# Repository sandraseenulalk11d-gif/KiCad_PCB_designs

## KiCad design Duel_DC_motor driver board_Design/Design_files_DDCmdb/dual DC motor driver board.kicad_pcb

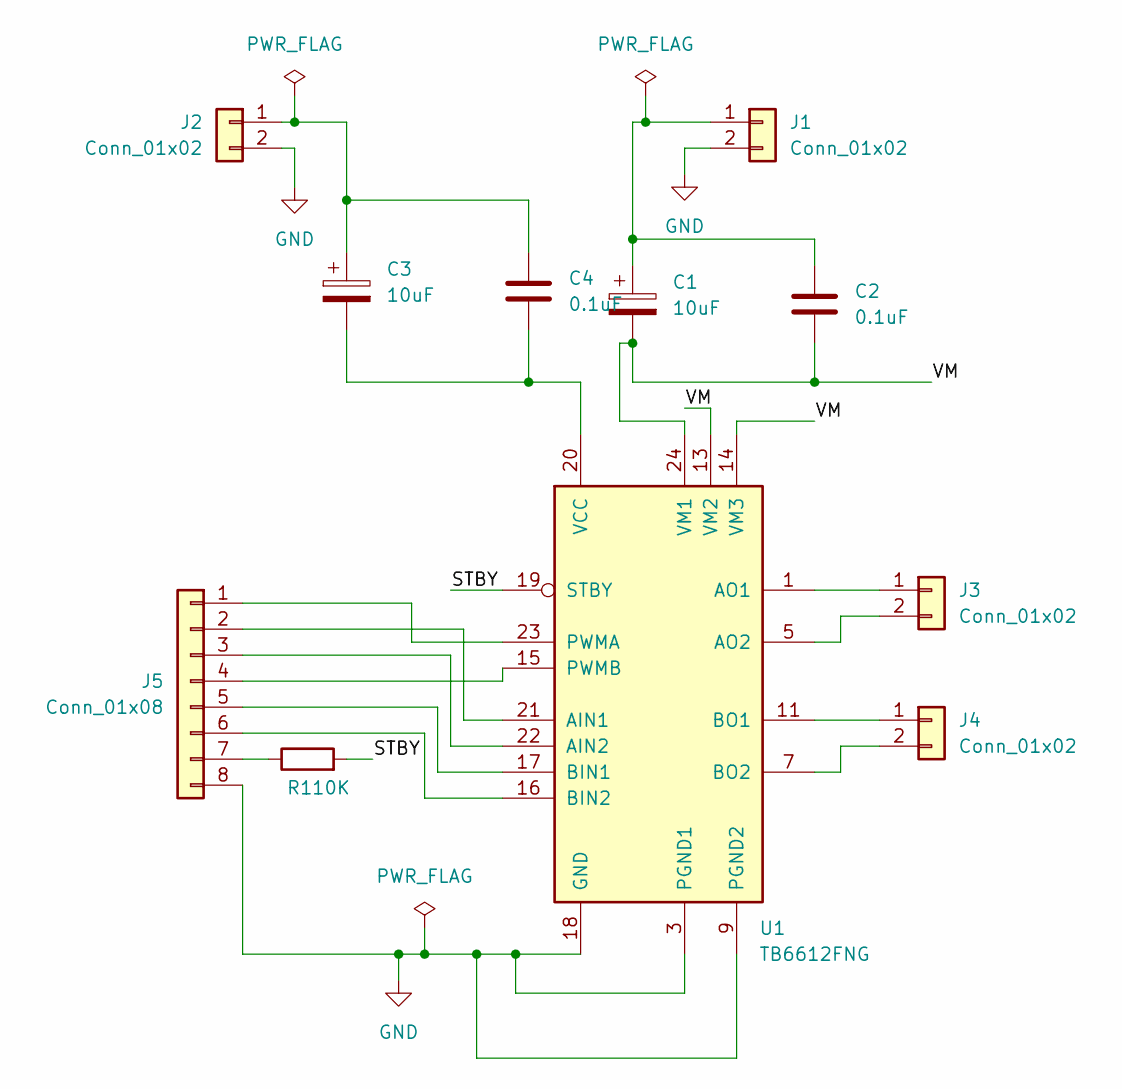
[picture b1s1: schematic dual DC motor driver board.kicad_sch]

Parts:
C1, C3: 10uF; CP_Radial_D5.0mm_P2.00mm
C2, C4: 0.1uF; C_0805_2012Metric
J1, J2, J3, J4: Conn_01x02; JST_XH_B2B-XH-A_1x02_P2.50mm_Vertical
J5: Conn_01x08; PinHeader_1x08_P2.54mm_Vertical
R1: 10K; R_0805_2012Metric
U1: TB6612FNG; SSOP-24_5.3x8.2mm_P0.65mm

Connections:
/STBY: R1.2, U1.19 (STBY)
/VM: C1.2, C2.2, U1.13 (VM2), U1.14 (VM3), U1.24 (VM1)
GND: J1.2, J2.2, J5.8, U1.3 (PGND1), U1.4 (PGND1), U1.9 (PGND2), U1.10 (PGND2), U1.18 (GND)
unnamed: C1.1, C2.1, J1.1
unnamed: C3.1, C4.1, J2.1
unnamed: J3.1, U1.1 (AO1), U1.2 (AO1)
unnamed: J3.2, U1.5 (AO2), U1.6 (AO2)
unnamed: J4.1, U1.11 (BO1), U1.12 (BO1)
unnamed: J4.2, U1.7 (BO2), U1.8 (BO2)
unnamed: J5.1, U1.23 (PWMA)
unnamed: J5.2, U1.21 (AIN1)
unnamed: J5.3, U1.22 (AIN2)
unnamed: J5.4, U1.15 (PWMB)
unnamed: J5.5, U1.17 (BIN1)
unnamed: J5.6, U1.16 (BIN2)
unnamed: J5.7, R1.1
unnamed: C3.2, C4.2, U1.20 (VCC)

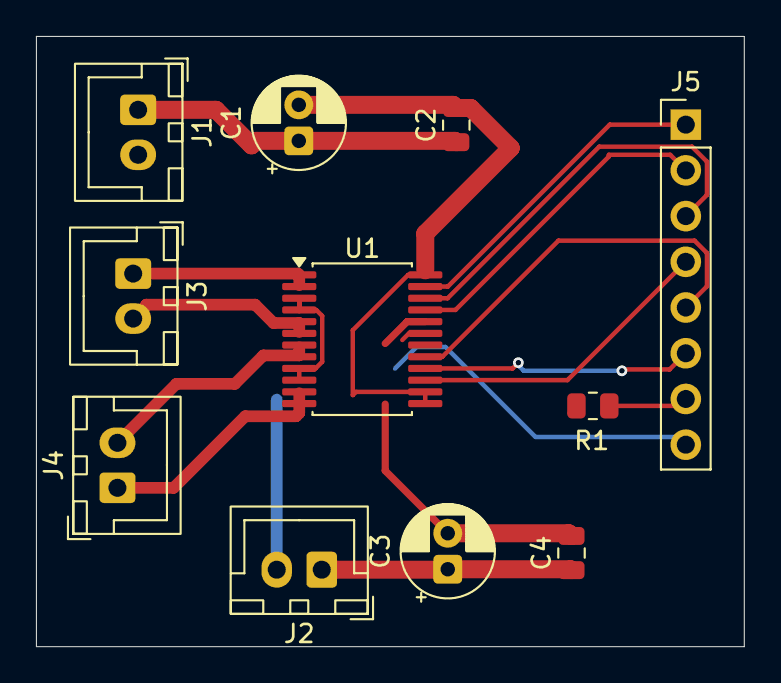
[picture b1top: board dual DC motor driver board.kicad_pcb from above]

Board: 2 copper layers, 39.3 x 33.9 mm, 11 parts (0 on the bottom side), 17 nets.

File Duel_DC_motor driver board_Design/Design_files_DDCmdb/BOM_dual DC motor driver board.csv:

"Reference","Qty","Value","DNP","Exclude from BOM","Exclude from Board","Footprint","Datasheet"
"C1,C3","2","10uF","","","","Capacitor_THT:CP_Radial_D5.0mm_P2.00mm",""
"C2,C4","2","0.1uF","","","","Capacitor_SMD:C_0805_2012Metric",""
"J1,J2,J3,J4","4","Conn_01x02","","","","Connector_JST:JST_XH_B2B-XH-A_1x02_P2.50mm_Vertical",""
"J5","1","Conn_01x08","","","","Connector_PinHeader_2.54mm:PinHeader_1x08_P2.54mm_Vertical",""
"R1","1","10K","","","","Resistor_SMD:R_0805_2012Metric",""
"U1","1","TB6612FNG","","","","Package_SO:SSOP-24_5.3x8.2mm_P0.65mm","https://toshiba.semicon-storage.com/us/product/linear/motord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"

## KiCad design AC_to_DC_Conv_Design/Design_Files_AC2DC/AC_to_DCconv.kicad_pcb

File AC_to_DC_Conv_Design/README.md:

# 230V AC to 5V DC Transformerless Power Supply

A compact, non-isolated capacitive dropper AC-DC power supply designed to provide low-current DC rails for microcontrollers and embedded sensors directly from single-phase utility mains.

---

## Technical Specifications

| Parameter | Value |
| :--- | :--- |
| **Input Voltage** | 230V AC ±10%, 50 Hz |
| **Output Voltage** | 5V DC (clamped and filtered) |
| **Output Current** | 30 mA – 40 mA continuous |
| **Topology** | Series capacitive dropper with full-bridge rectification and Zener shunt regulator |
| **Cooling** | Passive convection |

---

## Circuit Working & Key Stages

* **Capacitive Dropping Stage:** Uses the AC reactance ($X_C = \frac{1}{2\pi f C}$) of a high-voltage film capacitor to drop the mains voltage without the resistive heat dissipation of standard dropper resistors.
* **Transient & Inrush Suppression:** A flameproof fusible wirewound resistor limits high inrush current spikes during mains switch-on, paired with a metal-oxide varistor (MOV) to clamp utility voltage transients.
* **Discharge Mechanism:** A high-value bleeder resistor connected across the AC dropper capacitor ensures rapid discharge of stored energy when disconnected from mains.
* **Rectification & Filtering:** A full-wave diode bridge converts AC to pulsating DC, followed by an electrolytic reservoir capacitor with low ESR to smooth voltage ripple.
* **Regulation:** A precision Zener diode clamps the output rail, maintaining stable DC regulation across changing load currents.

---

## High-Voltage Safety Guidelines

* **Galvanic Isolation Warning:** This design contains **no isolation transformer**. The output DC ground rail floats directly at AC mains line potential.
* **Operational Hazard:** Direct contact with any point on this board during operation poses a severe electric shock risk.
* **Testing Requirement:** Always use an **isolated AC source (isolation transformer)** and an insulated probe setup during bench debugging and oscilloscope measurements.
* **Enclosure:** This module must be housed in a non-conductive, sealed plastic enclosure (flame-retardant ABS or polycarbonate) with no exposed metal headers or test pins.

---

## Repository Contents

* `/Design_Files_AC2DC` — Complete KiCad schematic (`.kicad_sch`), PCB layout (`.kicad_pcb`), and project configuration.
* `/Gerbers_AC2DC` — Production-ready Gerber files (copper layers, solder mask, silkscreen, and drill files).

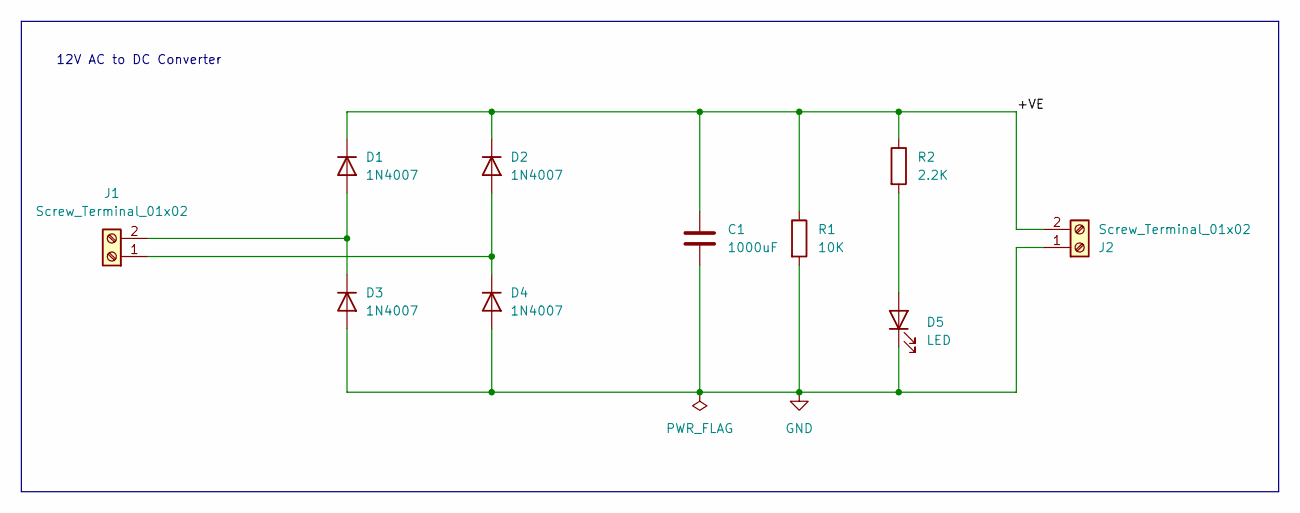
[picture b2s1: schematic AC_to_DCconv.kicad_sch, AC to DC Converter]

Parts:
C1: 1000uF; C_Radial_D8.0mm_H11.5mm_P3.50mm
D1, D2, D3, D4: 1N4007; D_DO-41_SOD81_P10.16mm_Horizontal
D5: LED; LED_D5.0mm
J1, J2: Screw_Terminal_01x02; TerminalBlock_Phoenix_MKDS-1,5-2-5.08_1x02_P5.08mm_Horizont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
R1: 10K; R_Axial_DIN0204_L3.6mm_D1.6mm_P7.62mm_Horizontal
R2: 2.2K; R_Axial_DIN0204_L3.6mm_D1.6mm_P7.62mm_Horizontal

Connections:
/+VE: C1.1, D1.1 (K), D2.1 (K), J2.2, R1.1, R2.1
GND: C1.2, D3.2 (A), D4.2 (A), D5.1 (K), J2.1, R1.2
unnamed: D1.2 (A), D3.1 (K), J1.2
unnamed: D2.2 (A), D4.1 (K), J1.1
unnamed: D5.2 (A), R2.2

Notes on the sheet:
12V AC to DC Converter

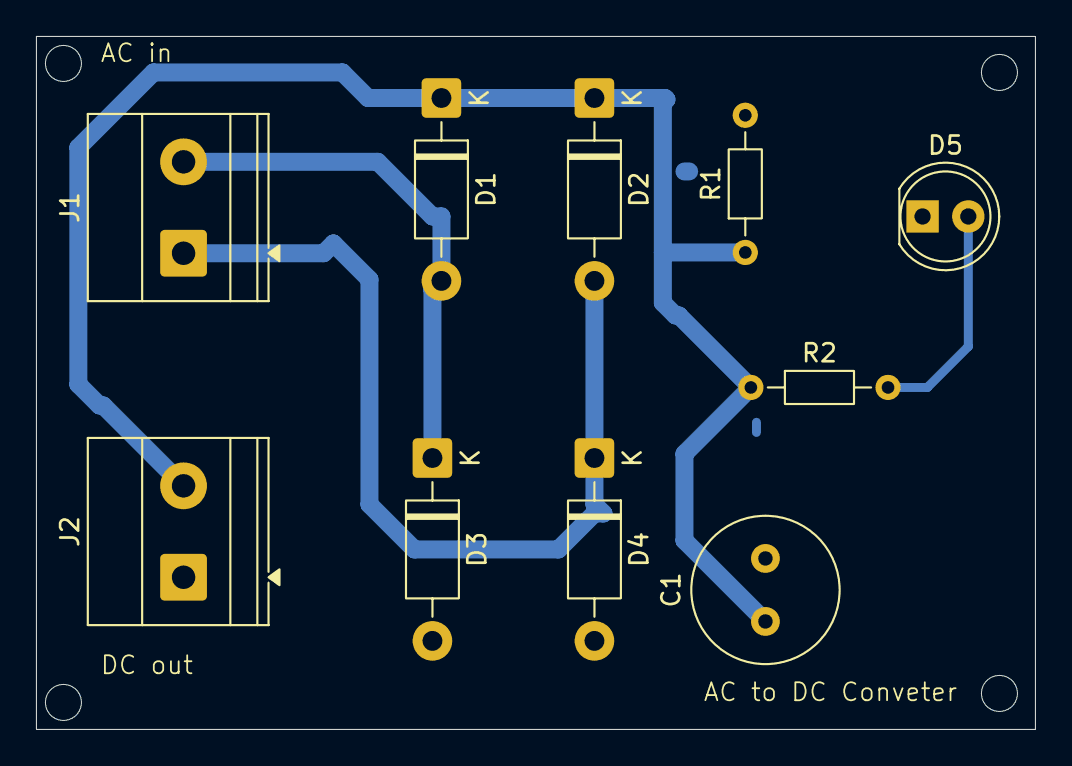
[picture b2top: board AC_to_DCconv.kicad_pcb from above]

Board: 2 copper layers, 55.5 x 38.5 mm, 10 parts (0 on the bottom side), 5 nets.

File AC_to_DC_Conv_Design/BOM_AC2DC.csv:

"Reference","Qty","Value","DNP","Exclude from BOM","Exclude from Board","Footprint","Datasheet"
"C1","1","1000uF","","","","Capacitor_THT:C_Radial_D8.0mm_H11.5mm_P3.50mm",""
"D1,D2,D3,D4","4","1N4007","","","","Diode_THT:D_DO-41_SOD81_P10.16mm_Horizontal","http://www.vishay.com/docs/88503/1n4001.pdf"
"D5","1","LED","","","","LED_THT:LED_D5.0mm",""
"J1,J2","2","Screw_Terminal_01x02","","","","TerminalBlock_Phoenix:TerminalBlock_Phoenix_MKDS-1,5-2-5.08_1x02_P5.08mm_Horizontal",""
"R1","1","10K","","","","Resistor_THT:R_Axial_DIN0204_L3.6mm_D1.6mm_P7.62mm_Horizontal",""
"R2","1","2.2K","","","","Resistor_THT:R_Axial_DIN0204_L3.6mm_D1.6mm_P7.62mm_Horizontal",""

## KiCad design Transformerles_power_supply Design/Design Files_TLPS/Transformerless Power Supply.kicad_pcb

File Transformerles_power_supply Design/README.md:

# Non-Isolated Capacitive Dropper Power Supply

A compact, transformerless AC-DC power supply designed to power low-current microcontroller and sensor circuits directly from 230V AC mains.

## Technical Specifications
- **Input Voltage:** 230V AC @ 50 Hz
- **Output:** 5V DC / ~30-50 mA
- **Topology:** Capacitive dropper with bridge rectification and Zener shunt regulation

## Safety & Component Implementation
- **Dropping Element:** Metallized polypropylene X2 safety capacitor
- **Shock Protection:** Bleeder resistor for passive capacitive discharge on disconnect
- **Transient & Surge Handling:** Inrush surge limiter resistor + MOV overvoltage clamp
- **Isolation Note:** Non-isolated topology; designed strictly for fully enclosed, touch-safe enclosures.

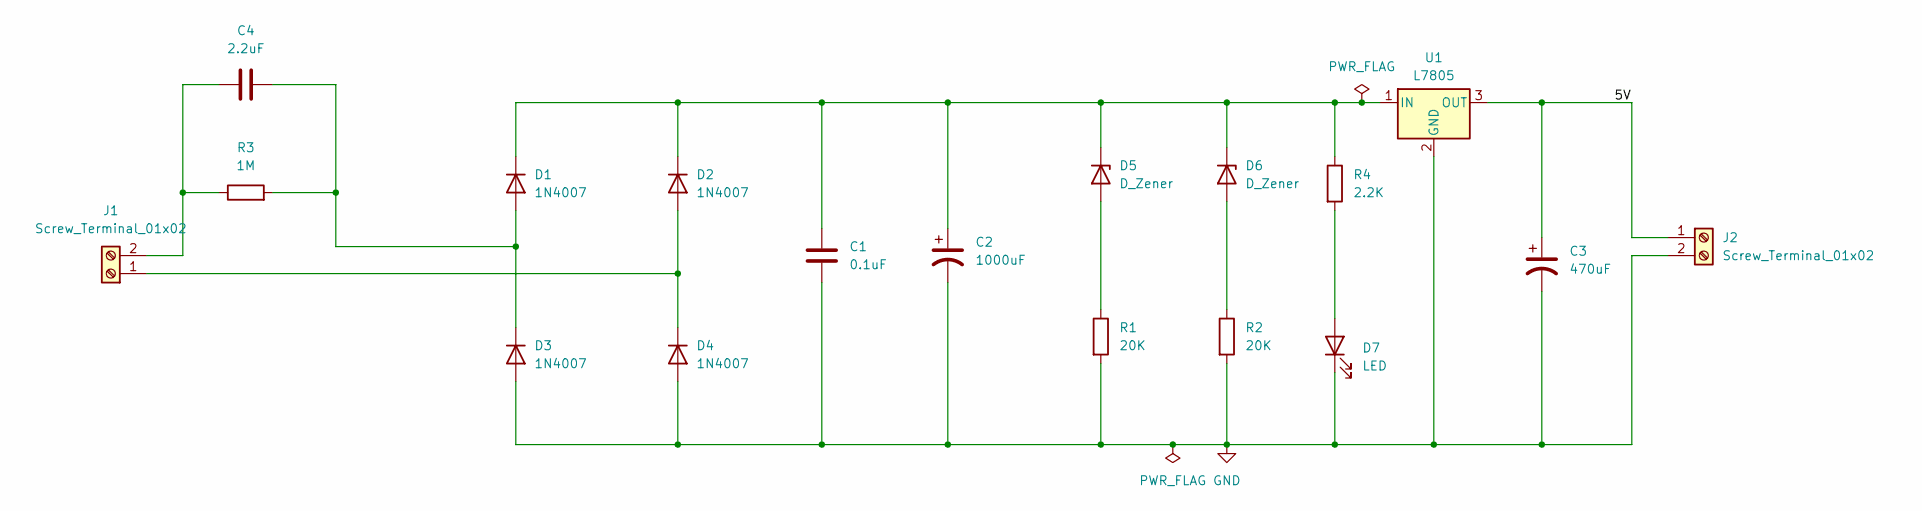
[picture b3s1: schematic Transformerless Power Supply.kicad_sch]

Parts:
C1: 0.1uF; C_Disc_D4.7mm_W2.5mm_P5.00mm
C2: 1000uF; CP_Radial_D10.0mm_P5.00mm
C3: 470uF; CP_Radial_D10.0mm_P3.80mm
C4: 2.2uF; C_Rect_L18.0mm_W6.0mm_P15.00mm_FKS3_FKP3
D1, D2, D3, D4: 1N4007; D_DO-41_SOD81_P10.16mm_Horizontal
D5, D6: D_Zener; D_A-405_P7.62mm_Horizontal
D7: LED; LED_D5.0mm
J1, J2: Screw_Terminal_01x02; TerminalBlock_Phoenix_MKDS-1,5-2-5.08_1x02_P5.08mm_Horizont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
R1, R2: 20K; R_Axial_DIN0207_L6.3mm_D2.5mm_P7.62mm_Horizontal
R3: 1M; R_Axial_DIN0207_L6.3mm_D2.5mm_P7.62mm_Horizontal
R4: 2.2K; R_Axial_DIN0207_L6.3mm_D2.5mm_P7.62mm_Horizontal
U1: L7805; TO-220-3_Vertical

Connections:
/5V: C3.1, J2.1, U1.3 (OUT)
GND: C1.2, C2.2, C3.2, D3.2 (A), D4.2 (A), D7.1 (K), J2.2, R1.2, R2.2, U1.2 (GND)
unnamed: C4.1, D1.2 (A), D3.1 (K), R3.2
unnamed: C1.1, C2.1, D1.1 (K), D2.1 (K), D5.1 (K), D6.1 (K), R4.1, U1.1 (IN)
unnamed: D2.2 (A), D4.1 (K), J1.1
unnamed: D5.2 (A), R1.1
unnamed: D6.2 (A), R2.1
unnamed: D7.2 (A), R4.2
unnamed: C4.2, J1.2, R3.1

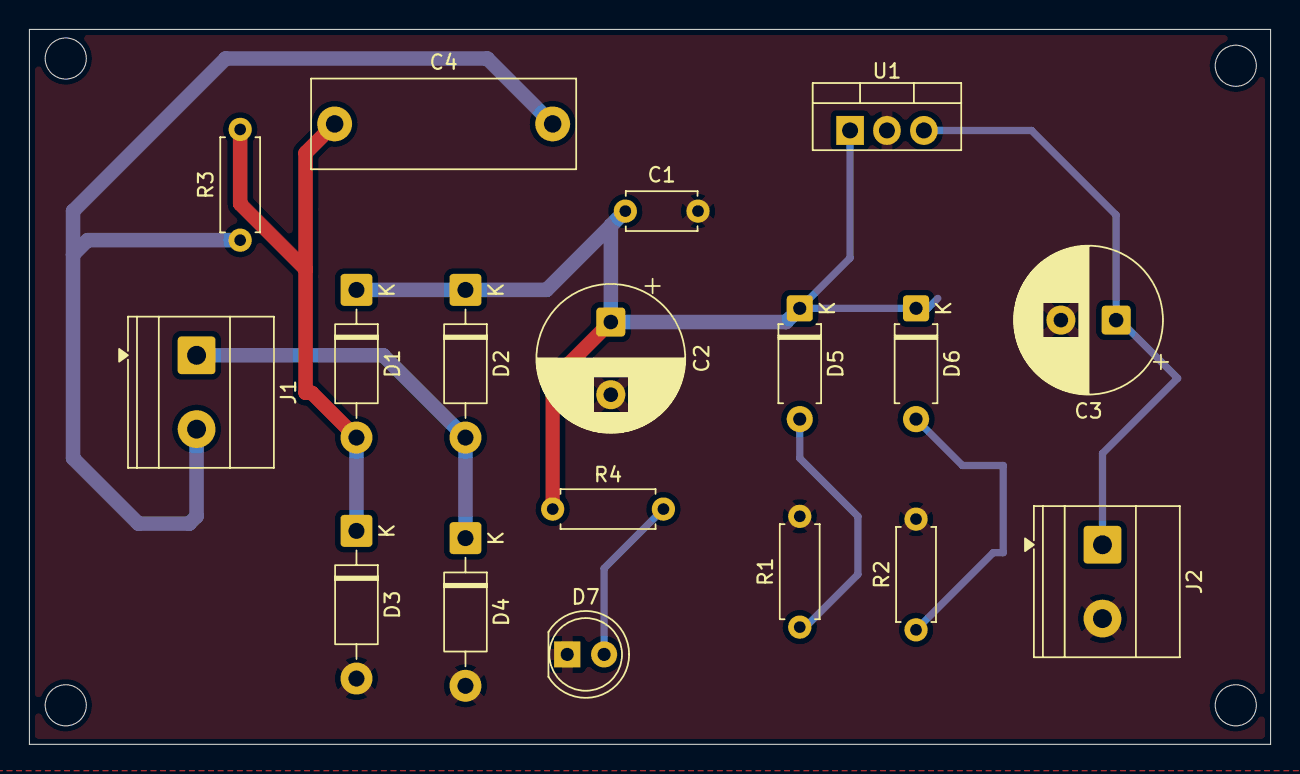
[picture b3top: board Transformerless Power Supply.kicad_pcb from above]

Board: 2 copper layers, 85.4 x 49.2 mm, 18 parts (0 on the bottom side), 9 nets.

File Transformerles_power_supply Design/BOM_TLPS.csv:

"Reference","Qty","Value","DNP","Exclude from BOM","Exclude from Board","Footprint","Datasheet"
"C1","1","0.1uF","","","","Capacitor_THT:C_Disc_D4.7mm_W2.5mm_P5.00mm",""
"C2","1","1000uF","","","","Capacitor_THT:CP_Radial_D10.0mm_P5.00mm",""
"C3","1","470uF","","","","Capacitor_THT:CP_Radial_D10.0mm_P3.80mm",""
"C4","1","2.2uF","","","","Capacitor_THT:C_Rect_L18.0mm_W6.0mm_P15.00mm_FKS3_FKP3",""
"D1,D2,D3,D4","4","1N4007","","","","Diode_THT:D_DO-41_SOD81_P10.16mm_Horizontal","http://www.vishay.com/docs/88503/1n4001.pdf"
"D5,D6","2","D_Zener","","","","Diode_THT:D_A-405_P7.62mm_Horizontal",""
"D7","1","LED","","","","LED_THT:LED_D5.0mm",""
"J1,J2","2","Screw_Terminal_01x02","","","","TerminalBlock_Phoenix:TerminalBlock_Phoenix_MKDS-1,5-2-5.08_1x02_P5.08mm_Horizontal",""
"R1,R2","2","20K","","","","Resistor_THT:R_Axial_DIN0207_L6.3mm_D2.5mm_P7.62mm_Horizontal",""
"R3","1","1M","","","","Resistor_THT:R_Axial_DIN0207_L6.3mm_D2.5mm_P7.62mm_Horizontal",""
"R4","1","2.2K","","","","Resistor_THT:R_Axial_DIN0207_L6.3mm_D2.5mm_P7.62mm_Horizontal",""
"U1","1","L7805","","","","Package_TO_SOT_THT:TO-220-3_Vertical","http://www.st.com/content/ccc/resource/technical/document/da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"

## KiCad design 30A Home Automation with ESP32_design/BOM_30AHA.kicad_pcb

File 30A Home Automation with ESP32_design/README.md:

# ESP32 30A Home Automation Controller

A custom industrial-grade controller board featuring ESP32 control, optoisolated relay driving, and GSM connectivity.

## Specifications & Features
- **Microcontroller:** ESP32-WROOM-32 (Wi-Fi / BLE)
- **Power Switching:** 30A high-power relays with PC817 optocoupler isolation
- **Cellular Connectivity:** SIM800 / Mini-SIM socket integration
- **Protection:** Flyback diodes, TVS diode arrays on I/O, and creepage isolation slots

## Repository Contents
- `/Design_files_30AHA`: KiCad schematic (`.kicad_sch`) and layout (`.kicad_pcb`)
- `/Gerbers_30AHA`: Manufacturing Gerbers (drill, copper, mask layers) and BOM

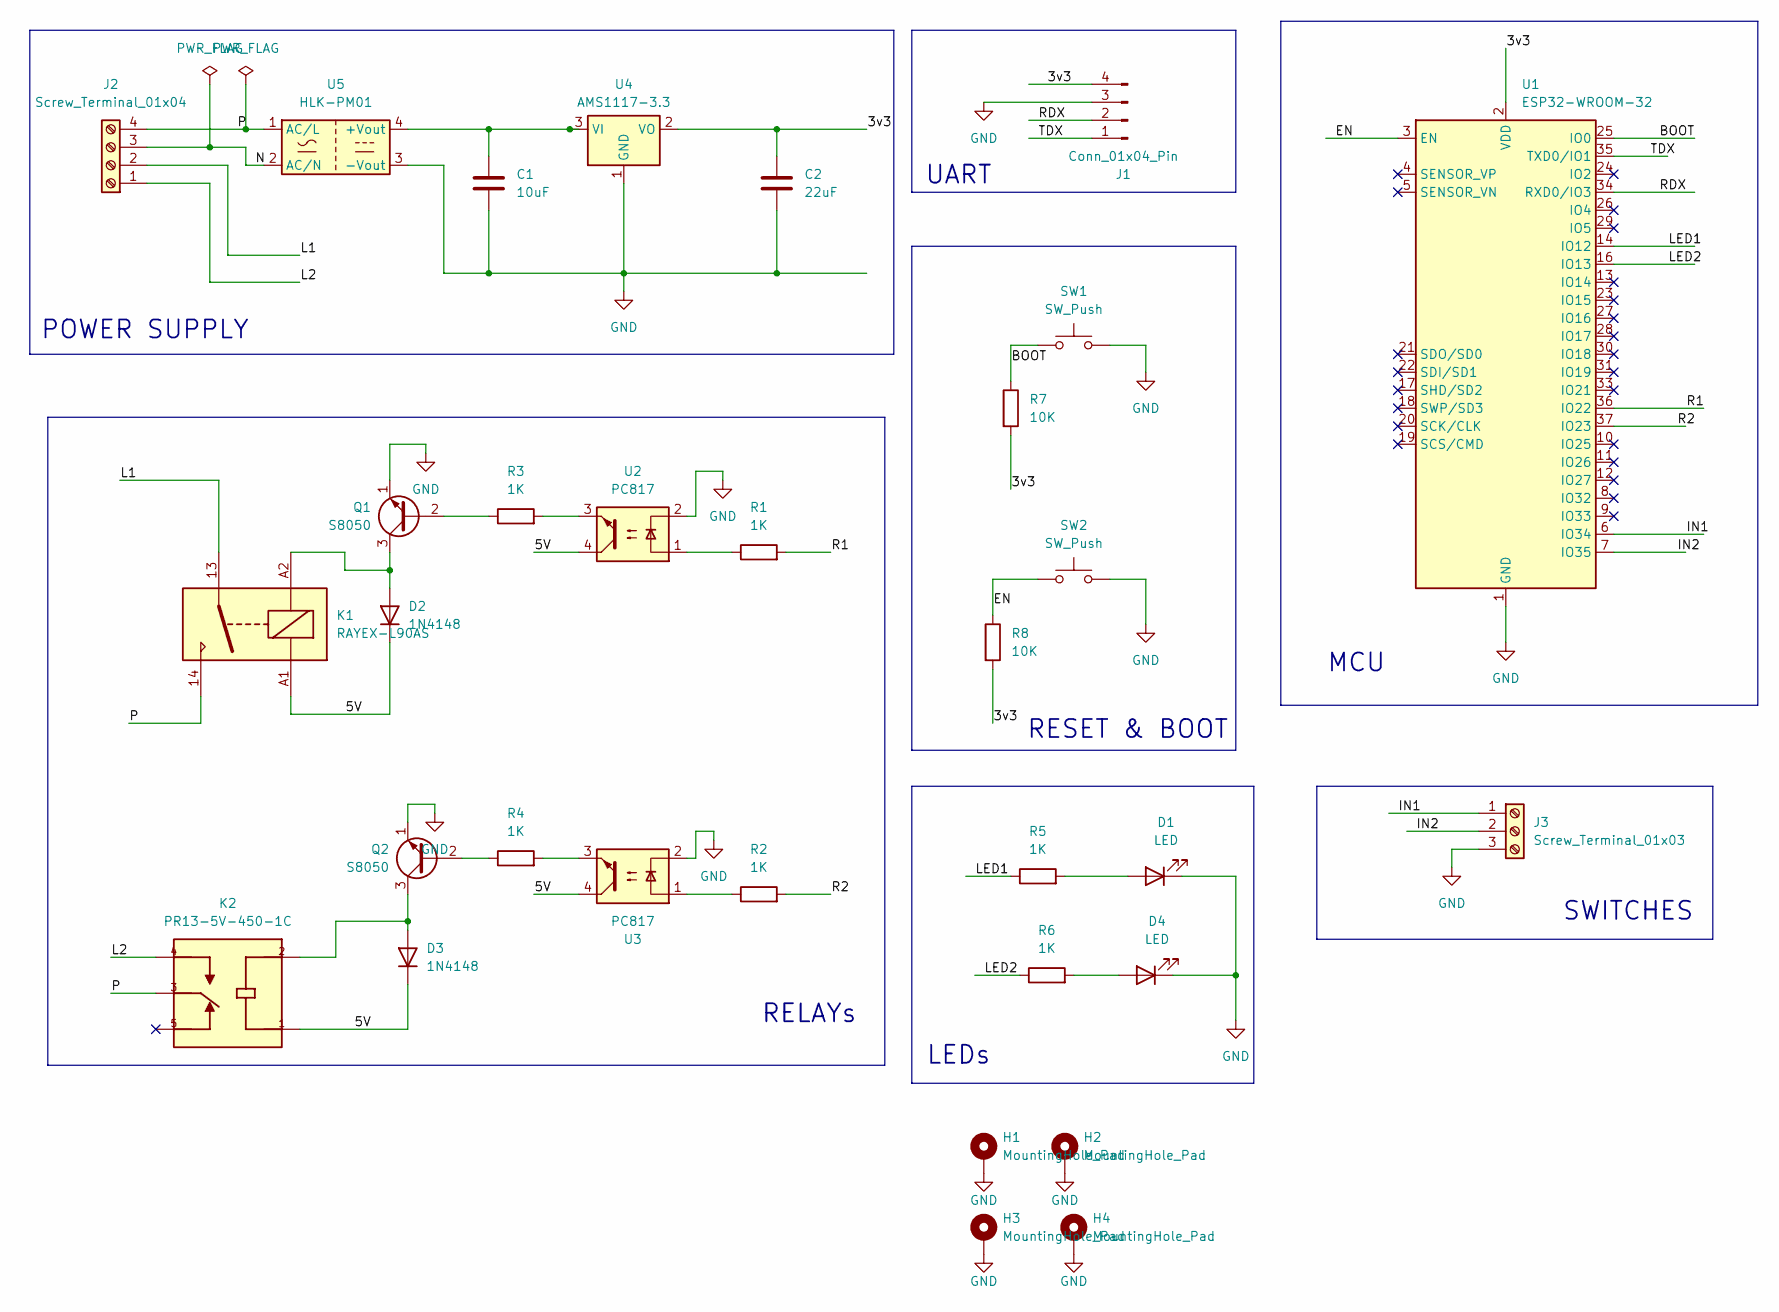
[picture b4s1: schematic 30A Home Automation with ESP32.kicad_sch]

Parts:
C1: 10uF; C_0805_2012Metric
C2: 22uF; C_0805_2012Metric
D1, D4: LED; LED_0805_2012Metric
D2, D3: 1N4148; D_DO-35_SOD27_P7.62mm_Horizontal
H1, H2, H3, H4: MountingHole_Pad; MountingHole_2.7mm_M2.5_Pad_Via
J1: Conn_01x04_Pin; PinHeader_1x04_P2.54mm_Vertical
J2: Screw_Terminal_01x04; TerminalBlock_Phoenix_MKDS-1,5-4-5.08_1x04_P5.08mm_Horizont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
J3: Screw_Terminal_01x03; TerminalBlock_Phoenix_MKDS-1,5-3_1x03_P5.00mm_Horizontal
K1: RAYEX-L90AS; Relay_SPST_RAYEX-L90AS
K2: PR13-5V-450-1C; Relay_SPDT_SANYOU_SRD_Series_Form_C; PARTREV 1.0
Q1, Q2: S8050; TO-92_Inline
R1, R2, R3, R4, R5, R6: 1K; R_0805_2012Metric
R7, R8: 10K; R_0805_2012Metric
SW1, SW2: SW_Push; SW_PUSH_6mm
U1: ESP32-WROOM-32
U2, U3: PC817; DIP-4_W7.62mm
U4: AMS1117-3.3; SOT-223-3_TabPin2
U5: HLK-PM01; Converter_ACDC_Hi-Link_HLK-PMxx

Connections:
/3v3: C2.1, J1.4, R7.2, R8.2, U1.2 (VDD), U4.2 (VO)
/5V: D2.1 (K), D3.1 (K), K1.A1, K2.1, U2.4, U3.4
/BOOT: R7.1, SW1.1, U1.25 (IO0)
/EN: R8.1, SW2.1, U1.3 (EN)
/IN1: J3.1, U1.6 (IO34)
/IN2: J3.2, U1.7 (IO35)
/L1: J2.2, K1.13
/L2: J2.1, K2.4
/LED1: R5.1, U1.14 (IO12)
/LED2: R6.1, U1.16 (IO13)
/R1: R1.2, U1.36 (IO22)
/R2: R2.2, U1.37 (IO23)
/RDX: J1.2, U1.34 (RXD0/IO3)
/TDX: J1.1, U1.35 (TXD0/IO1)
GND: C1.2, C2.2, D1.1 (K), D4.1 (K), H1.1 (1_1), H2.1 (1_1), H3.1 (1_1), H4.1 (1_1), J1.3, J3.3, Q1.1 (E), Q2.1 (E), SW1.2, SW2.2, U1.1 (GND), U1.15 (GND), U1.38 (GND), U1.39 (GND), U2.2, U3.2, U4.1 (GND), U5.3 (-Vout)
unnamed: D1.2 (A), R5.2
unnamed: D2.2 (A), K1.A2, Q1.3 (C)
unnamed: D3.2 (A), K2.2, Q2.3 (C)
unnamed: D4.2 (A), R6.2
unnamed: Q1.2 (B), R3.1
unnamed: Q2.2 (B), R4.1
unnamed: R1.1, U2.1
unnamed: R2.1, U3.1
unnamed: R3.2, U2.3
unnamed: R4.2, U3.3
unnamed: C1.1, U4.3 (VI), U5.4 (+Vout)

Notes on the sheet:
SWITCHES
LEDs
UART
MCU
POWER SUPPLY
RELAYs
RESET & BOOT

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
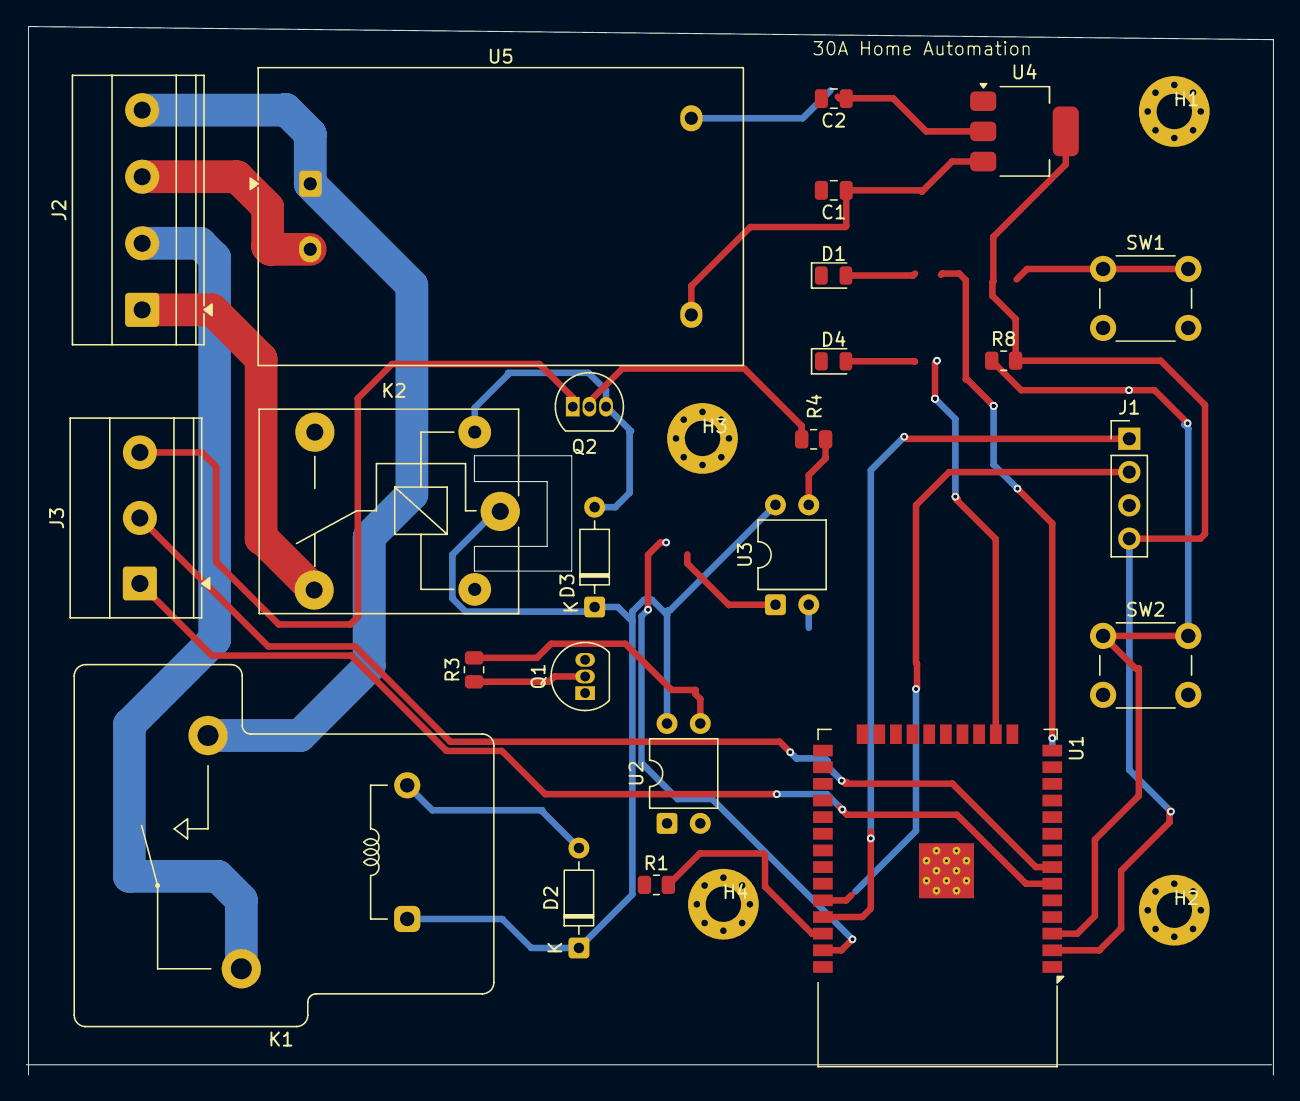
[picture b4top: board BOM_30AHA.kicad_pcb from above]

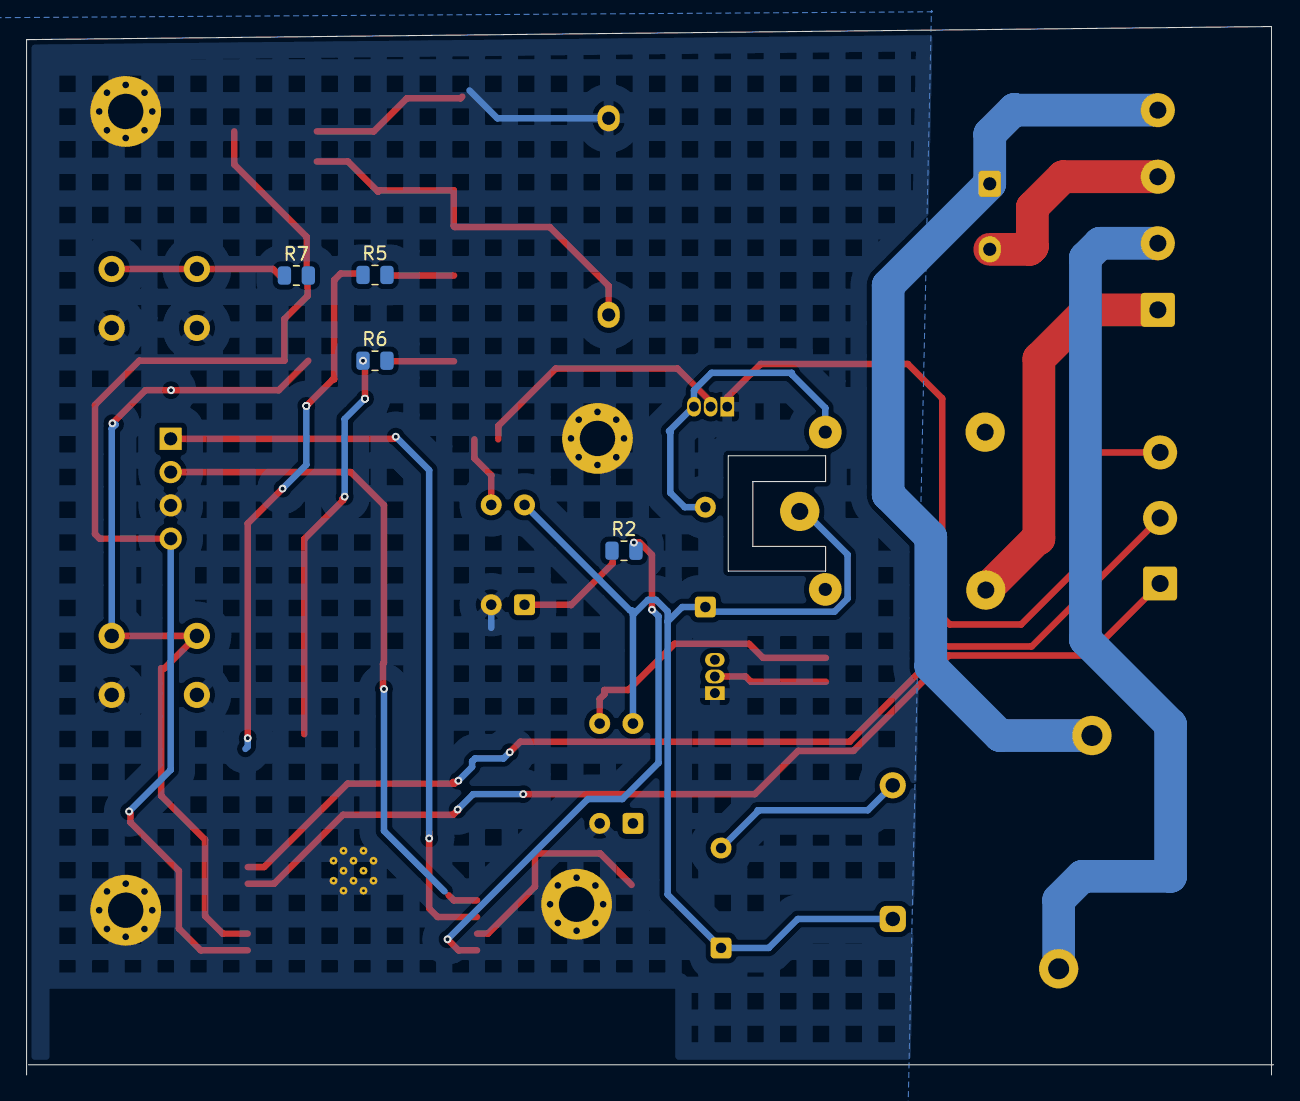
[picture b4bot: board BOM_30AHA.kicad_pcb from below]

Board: 2 copper layers, 95.2 x 80.0 mm, 32 parts (4 on the bottom side), 28 nets.
